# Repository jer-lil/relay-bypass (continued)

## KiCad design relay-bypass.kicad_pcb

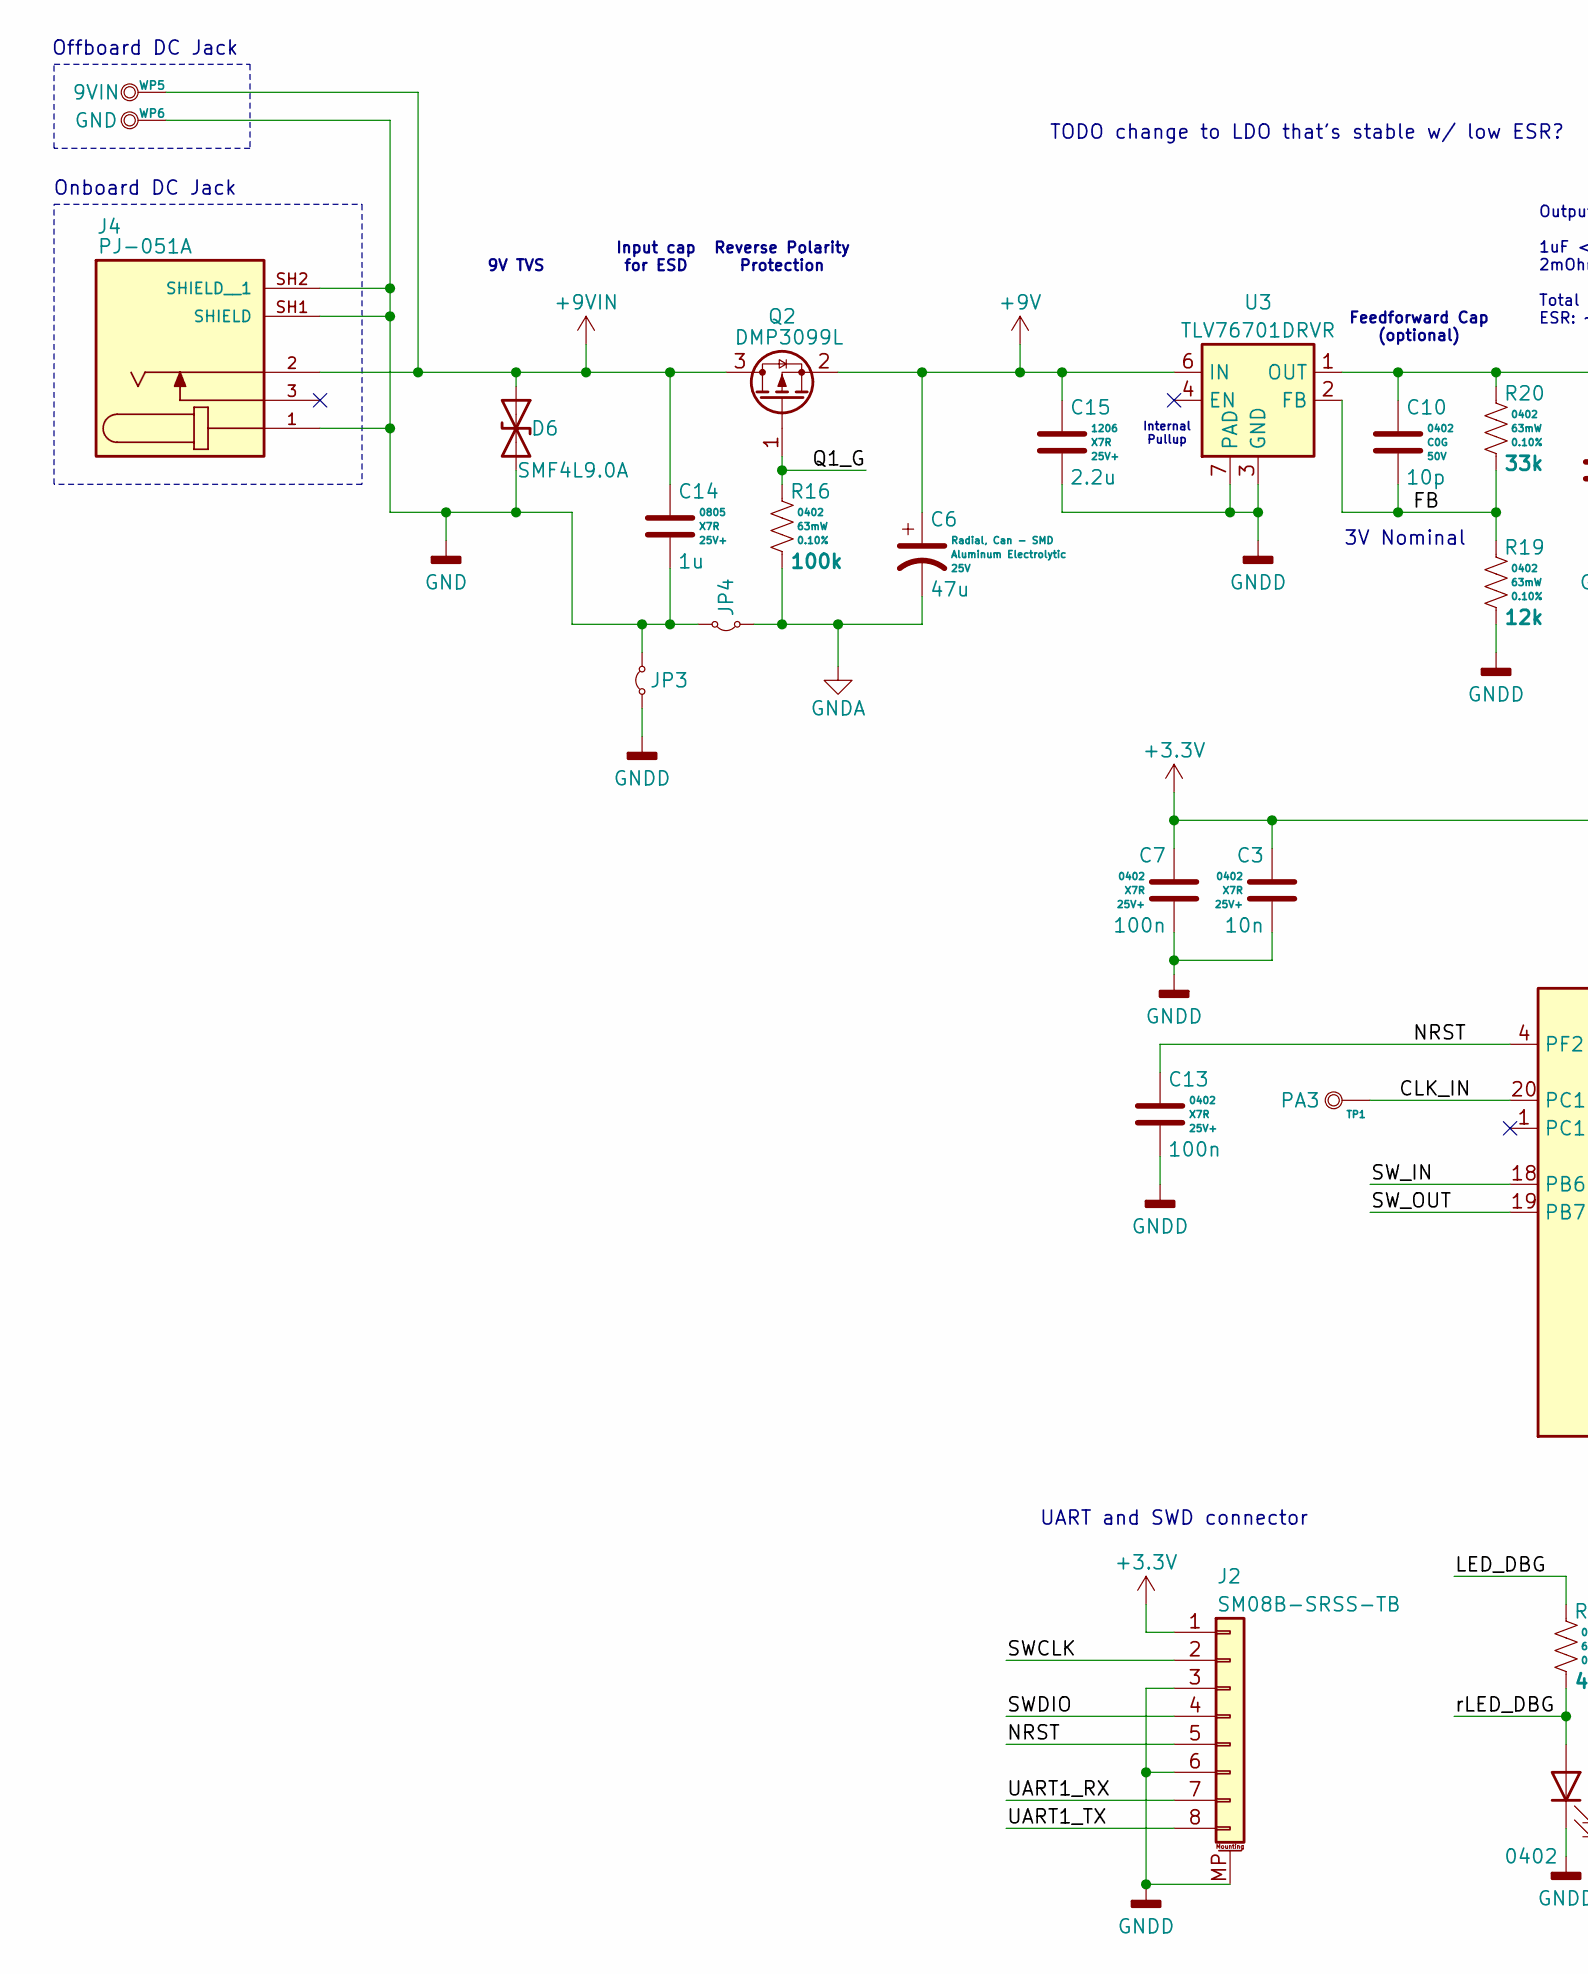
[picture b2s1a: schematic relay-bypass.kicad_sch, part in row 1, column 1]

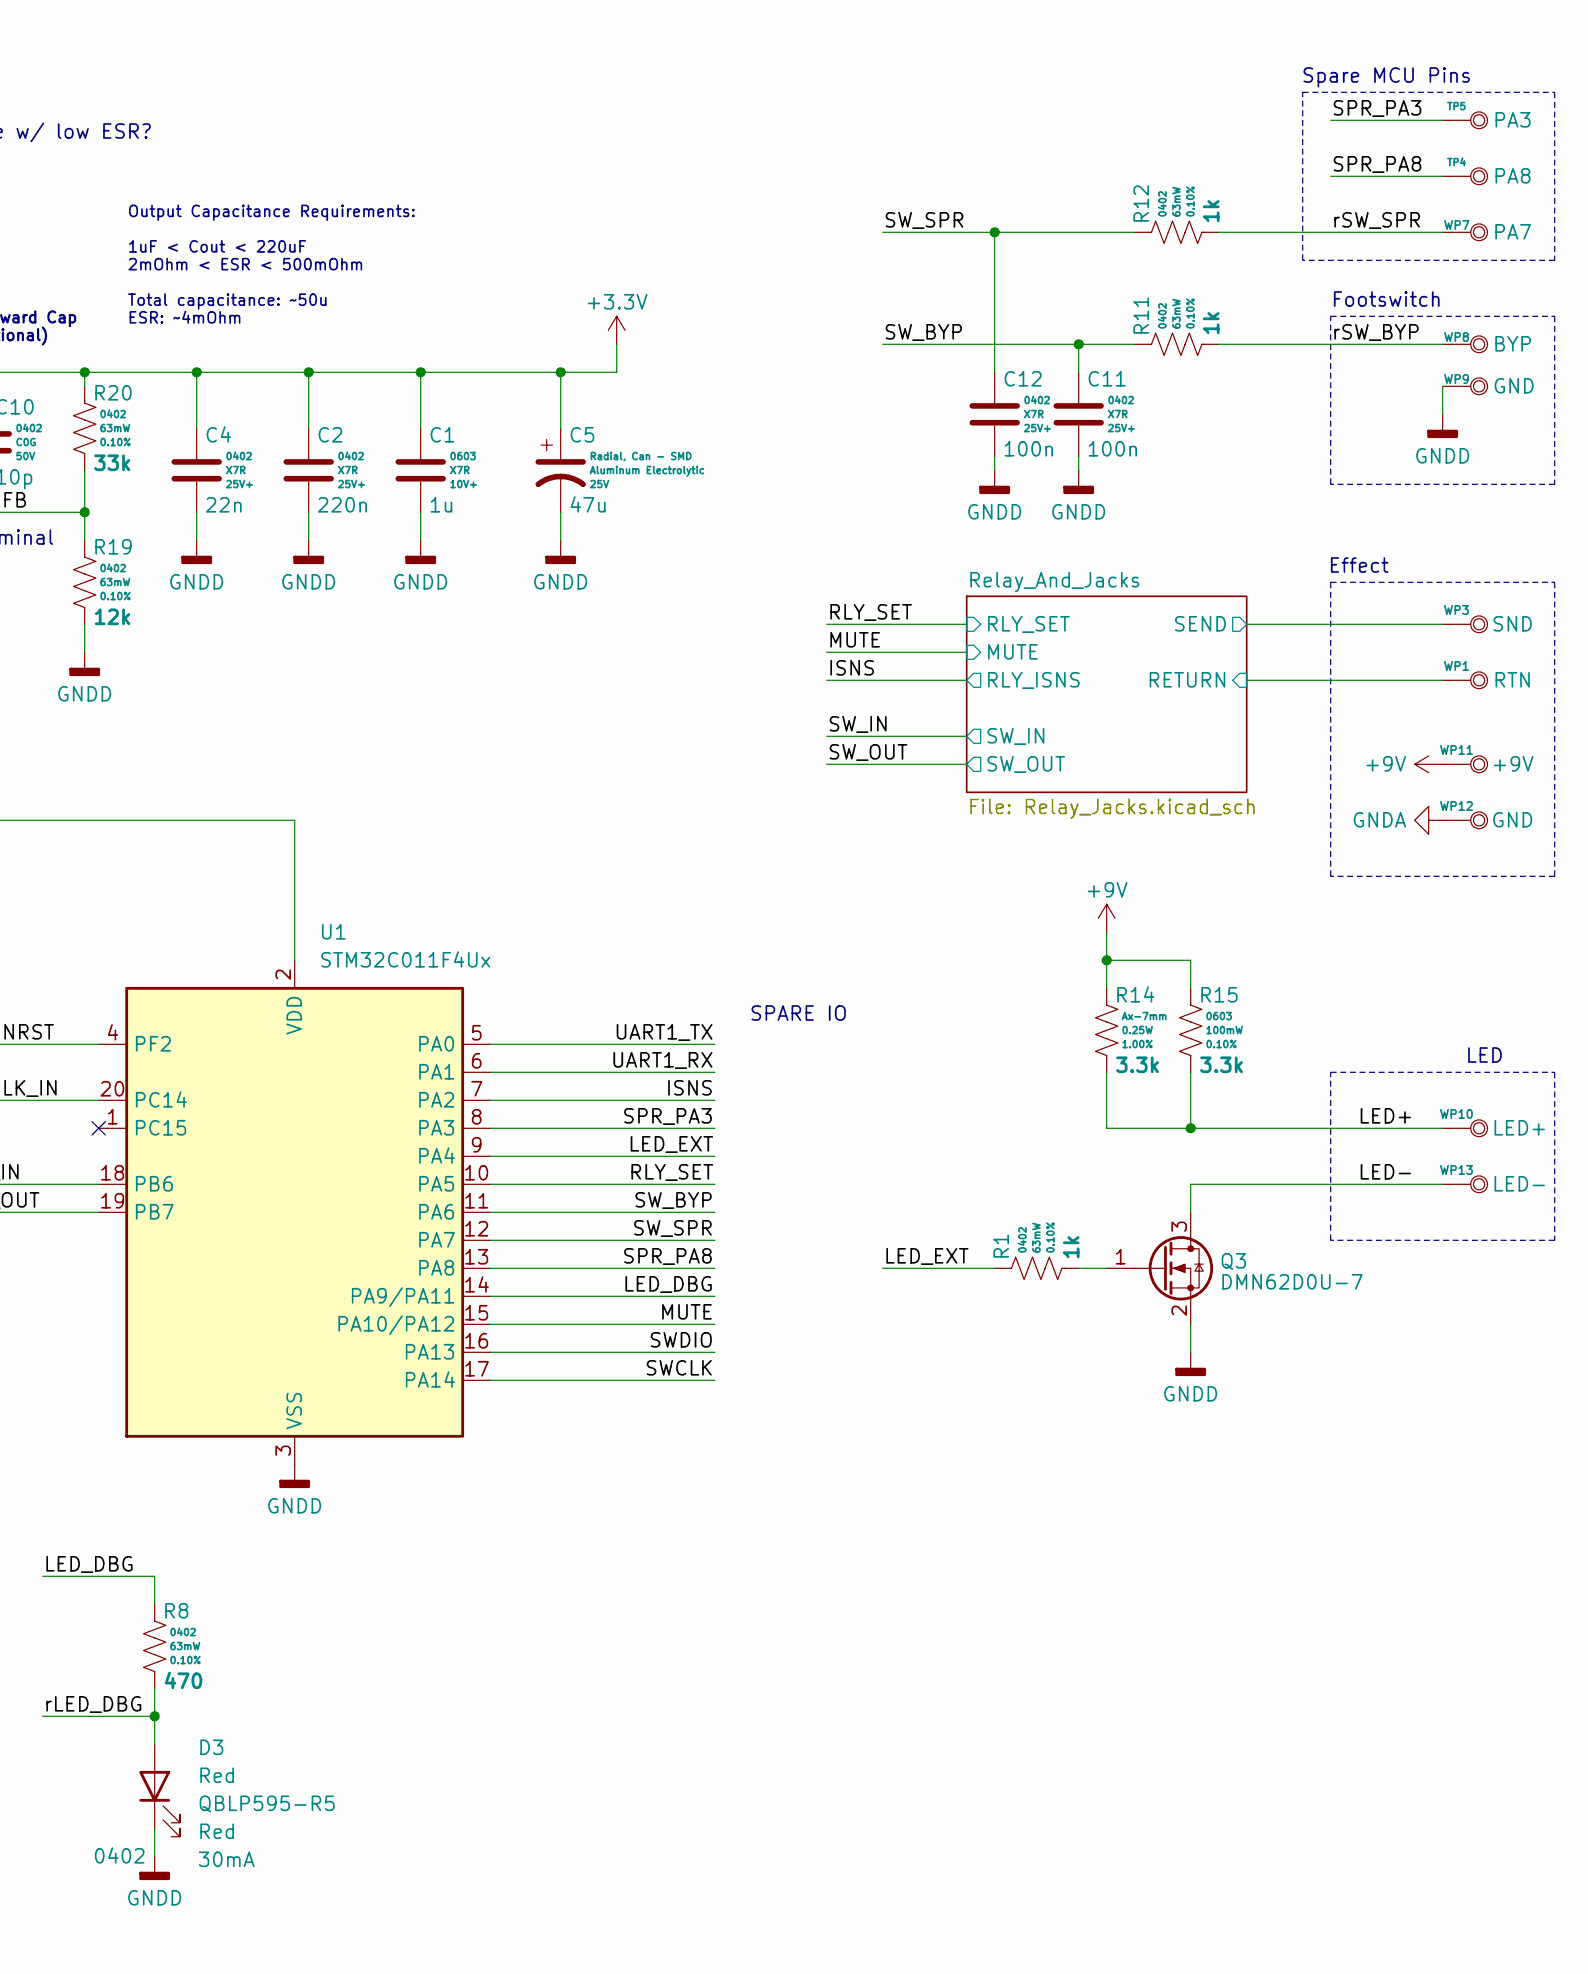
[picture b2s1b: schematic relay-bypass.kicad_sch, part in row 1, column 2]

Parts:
C1: 1u; C_0603_1608Metric; Voltage 10V+; Tolerance 10%; MPN C0603C105K8RACTU
C2: 220n; C_0402_1005Metric; Voltage 25V+; Tolerance 10%; MPN C0402C224K3RACTU
C3: 10n; C_0402_1005Metric; Voltage 25V+; Tolerance 10%; MPN C0402C103K3RACTU
C4: 22n; C_0402_1005Metric; Voltage 25V+; Tolerance 10%; MPN C0402C223K3RACTU
C5, C6: 47u; CP_Elec_6.3x5.8; Voltage 25V; Tolerance +/-20%; MPN EEE-FK1E470P
C7, C11, C12, C13: 100n; C_0402_1005Metric; Voltage 25V+; Tolerance 10%; MPN C0402C104K3RACTU
C10: 10p; C_0402_1005Metric; Voltage 50V; Tolerance +/-2%; MPN GRM1555C1H100GA01D
C14: 1u; C_0805_2012Metric; Voltage 25V+; Tolerance 10%; MPN C0805C105K3RACTU
C15: 2.2u; C_1206_3216Metric; Voltage 25V+; Tolerance 10%; MPN C1206C225K3RACTU
D3: Red; LED_0402_1005Metric; MPN QBLP595-R5
D6: SMF4L9.0A; D_SOD-123F; MPN SMF4L9.0A
J2: 8; JST_SH_BM08B-SRSS-TB_1x08-1MP_P1.00mm_Vertical; MPN SM08B-SRSS-TB
J4: 3; BarrelJack_CUI_PJ-051A; PARTREV 1.06
JP3, JP4: Jumper_2_Small_Bridged; SolderJumper-2_P1.3mm_Bridged2Bar_Pad1.0x1.5mm
Q2: DMP3099L; SOT-23; MPN DMP3099L
Q3: DMN62D0U-7; SOT-23; MPN DMN62D0U-7
R1, R11, R12: 1k; R_0402_1005Metric; Tolerance 0.10%; Voltage 50V; MPN RT0402BRD071KL
R8: 470; R_0402_1005Metric; Tolerance 0.10%; Voltage 50V; MPN RT0402BRD07470RL
R14: 3.3k; R_Axial_DIN0207_L6.3mm_D2.5mm_P7.5mm_Horizontal; Tolerance 1.00%; Voltage 250V; MPN MFR-25FBF52-3K3
R15: 3.3k; R_0603_1608Metric; Tolerance 0.10%; Voltage 75V; MPN RT0603BRD073K3L
R16: 100k; R_0402_1005Metric; Tolerance 0.10%; Voltage 50V; MPN RT0402BRD07100KL
R19: 12k; R_0402_1005Metric; Tolerance 0.10%; Voltage 50V; MPN RT0402BRD0712KL
R20: 33k; R_0402_1005Metric; Tolerance 0.10%; Voltage 50V; MPN RT0402BRD0733KL
TP1, TP5: PA3; TestPoint_PTH_H1.02mm_NoOutline
TP4: PA8; TestPoint_PTH_H1.02mm_NoOutline
U1: STM32C011F4Ux; ST_UFQFPN-20_3x3mm_P0.5mm
U3: TLV76701DRVR; WSON-6-1EP_2x2mm_P0.65mm_EP1x1.6mm; Voltage ADJ; MPN TLV76701DRVR
WP1: RTN; WirePad_H0.95mm_22-24AWG
WP3: SND; WirePad_H0.95mm_22-24AWG
WP5: 9VIN; WirePad_H0.95mm_22-24AWG
WP6, WP9, WP12: GND; WirePad_H0.95mm_22-24AWG
WP7: PA7; WirePad_H0.95mm_22-24AWG
WP8: BYP; WirePad_H0.95mm_22-24AWG
WP10: LED+; WirePad_H0.95mm_22-24AWG
WP11: +9V; WirePad_H0.95mm_22-24AWG
WP13: LED-; WirePad_H0.95mm_22-24AWG

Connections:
+3.3V: C1.1, C2.1, C3.1, C4.1, C5.1, C7.1, C10.1, J2.1, R20.1, U1.2 (VDD), U3.1 (OUT); also elsewhere on the board
+9V: C6.1, C15.1, Q2.2 (S), R14.1, R15.1, U3.6 (IN), WP11.1; also elsewhere on the board
+9VIN: C14.1, D6.1 (A1), J4.2, Q2.3 (D), WP5.1
/CLK_IN: TP1.1, U1.20 (PC14)
/FB: C10.2, R19.1, R20.2, U3.2 (FB)
/ISNS: U1.7 (PA2); also elsewhere on the board
/LED+: R14.2, R15.2, WP10.1
/LED-: Q3.3 (D), WP13.1
/LED_DBG: R8.1, U1.14 (PA9/PA11)
/LED_EXT: R1.1, U1.9 (PA4)
/MUTE: U1.15 (PA10/PA12); also elsewhere on the board
/NRST: C13.1, J2.5, U1.4 (PF2)
/Q1_G: Q2.1 (G), R16.1
/RLY_SET: U1.10 (PA5); also elsewhere on the board
/Relay_And_Jacks/RETURN: WP1.1; also elsewhere on the board
/Relay_And_Jacks/SEND: WP3.1; also elsewhere on the board
/SPR_PA3: TP5.1, U1.8 (PA3)
/SPR_PA8: TP4.1, U1.13 (PA8)
/SWCLK: J2.2, U1.17 (PA14)
/SWDIO: J2.4, U1.16 (PA13)
/SW_BYP: C11.1, R11.1, U1.11 (PA6)
/SW_IN: U1.18 (PB6); also elsewhere on the board
/SW_OUT: U1.19 (PB7); also elsewhere on the board
/SW_SPR: C12.1, R12.1, U1.12 (PA7)
/UART1_RX: J2.7, U1.6 (PA1)
/UART1_TX: J2.8, U1.5 (PA0)
/rLED_DBG: D3.2 (A), R8.2
/rSW_BYP: R11.2, WP8.1
/rSW_SPR: R12.2, WP7.1
GND: C14.2, D6.2 (A2), J4.1, J4.SH1 (SHIELD), J4.SH2 (SHIELD__1), JP3.2 (B), JP4.2 (B), WP6.1
GNDA: C6.2, JP4.1 (A), R16.2, WP12.1; also elsewhere on the board
GNDD: C1.2, C2.2, C3.2, C4.2, C5.2, C7.2, C11.2, C12.2, C13.2, C15.2, D3.1 (K), J2.3, J2.6, J2.MP (MountPin), JP3.1 (A), Q3.2 (S), R19.2, U1.3 (VSS), U3.3 (GND), U3.5 (GND), U3.7 (PAD), WP9.1; also elsewhere on the board
unnamed: Q3.1 (G), R1.2

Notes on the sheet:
Input cap for ESD
UART and SWD connector
Spare MCU Pins
Effect
9V TVS
TODO change to LDO that's stable w/ low ESR?
Reverse Polarity Protection
3V Nominal
Output Capacitance Requirements: 1uF < Cout < 220uF 2mOhm < ESR < 500mOhm Total capacitance: ~50u ESR: ~4mOhm
LED
Footswitch
Feedforward Cap (optional)
SPARE IO
Onboard DC Jack
Internal Pullup
Offboard DC Jack

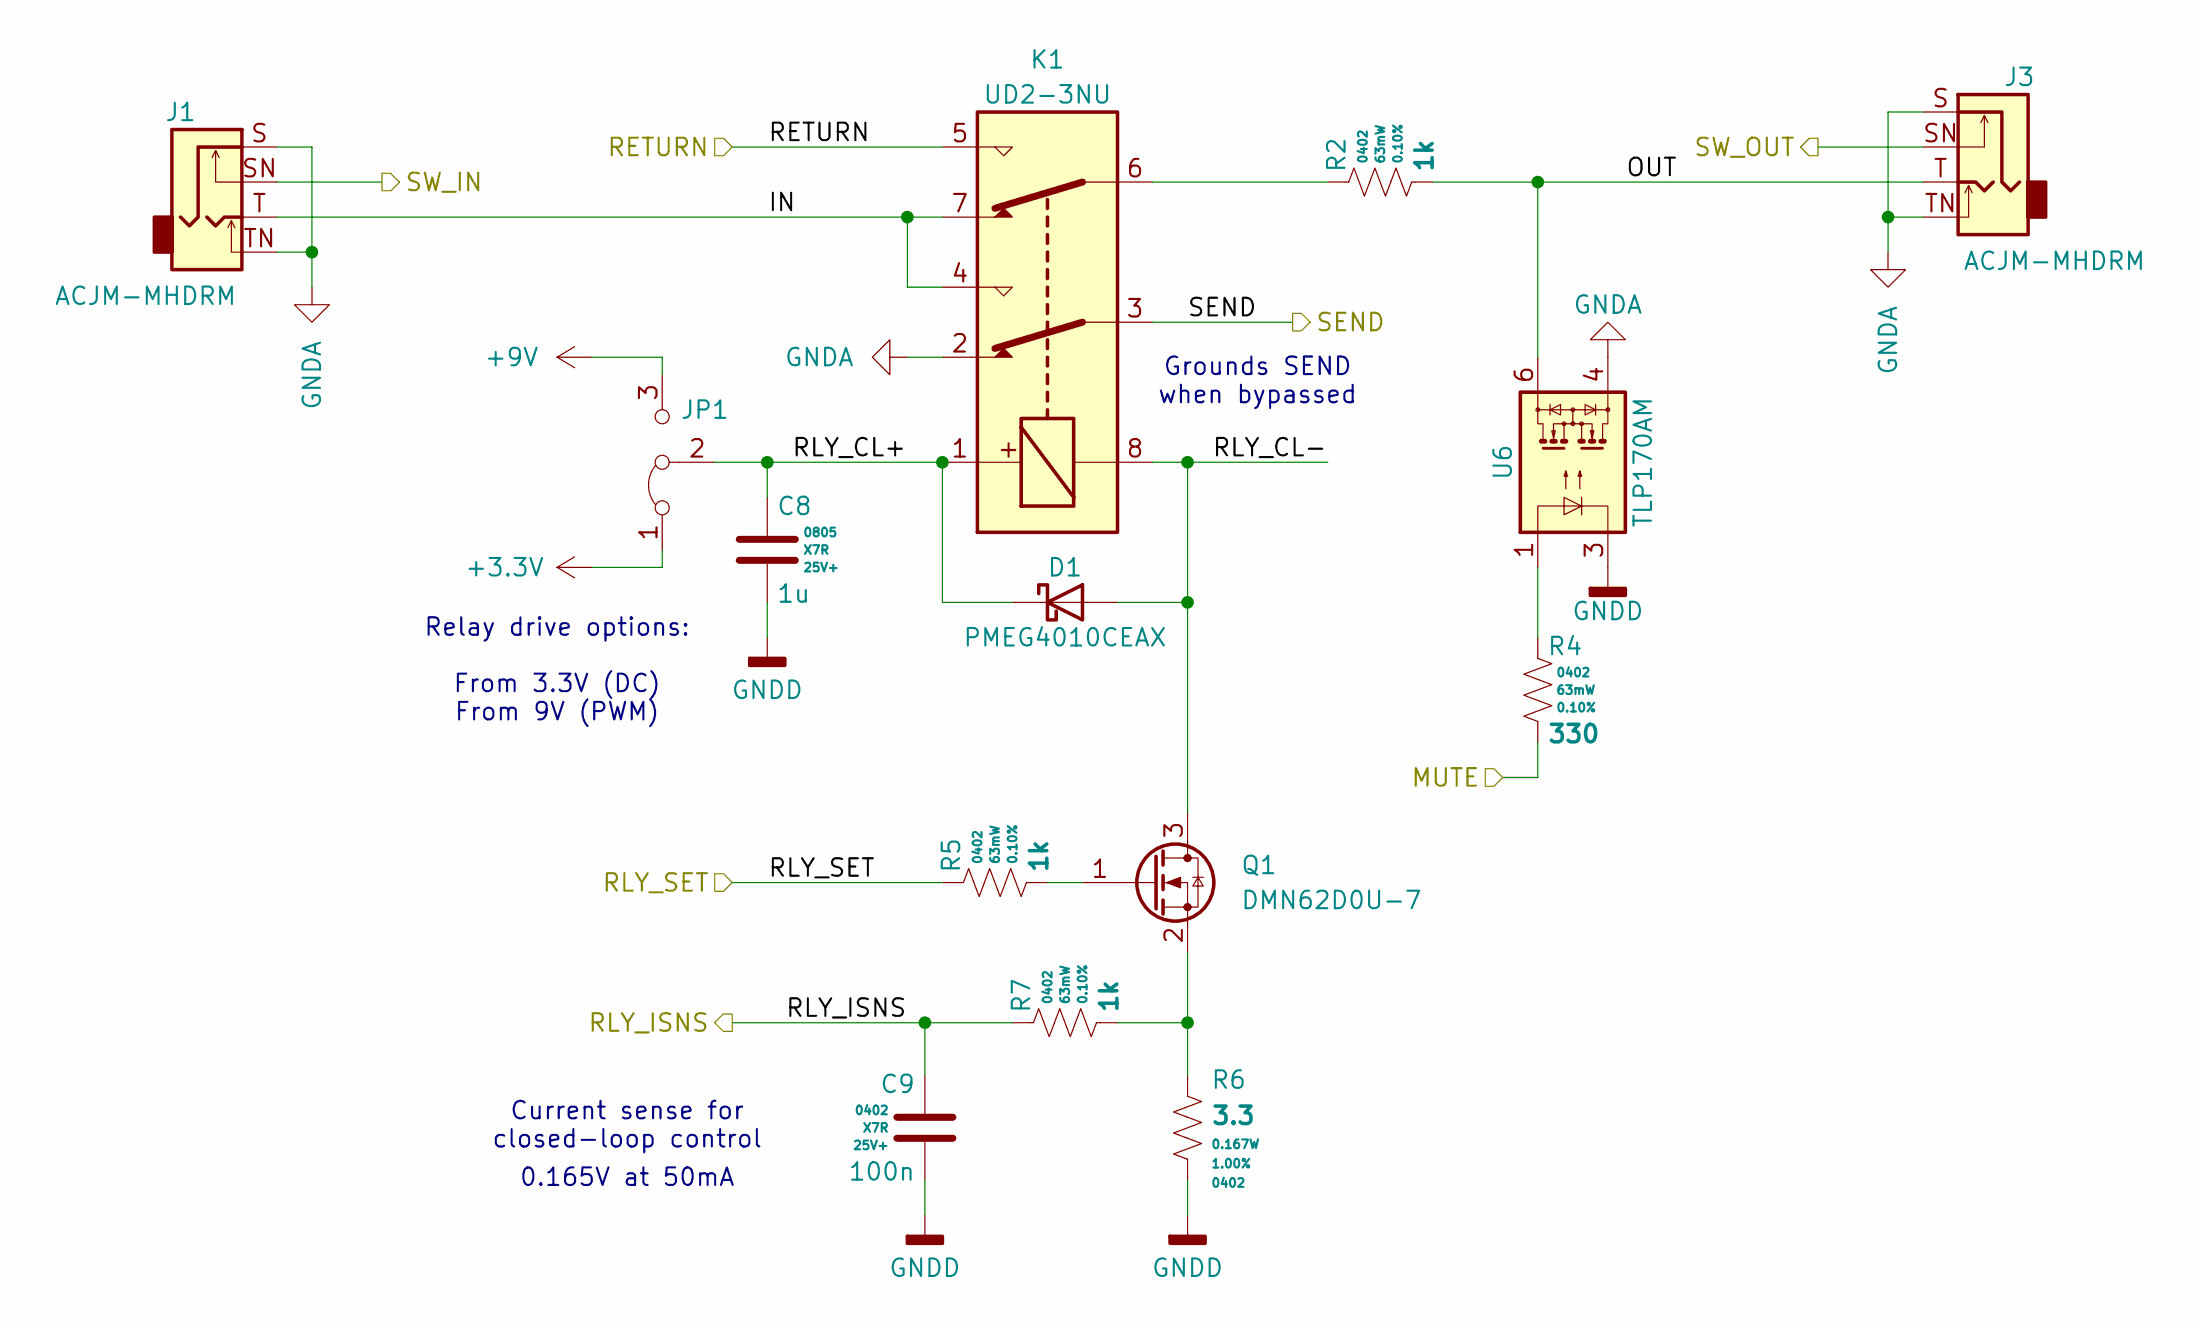
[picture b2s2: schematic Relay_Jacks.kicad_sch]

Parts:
C8: 1u; C_0805_2012Metric; Voltage 25V+; Tolerance 10%; MPN C0805C105K3RACTU
C9: 100n; C_0402_1005Metric; Voltage 25V+; Tolerance 10%; MPN C0402C104K3RACTU
D1: PMEG4010CEAX; D_SOD-323; Voltage 840 mV @ 1 A; MPN PMEG4010CEAX
J1, J3: 4; Amphenol_ACJM-MHDR(M); MPN ACJM-MHDRM
JP1: Jumper_3_Bridged12; SolderJumper-3_P1.3mm_Bridged12_Pad1.0x1.5mm
K1: IM05JR; UD23NU; MPN UD2-3NU
Q1: DMN62D0U-7; SOT-23; MPN DMN62D0U-7
R2, R5, R7: 1k; R_0402_1005Metric; Tolerance 0.10%; Voltage 50V; MPN RT0402BRD071KL
R4: 330; R_0402_1005Metric; Tolerance 0.10%; Voltage 50V; MPN RT0402BRD07330RL
R6: 3.3; R_0402_1005Metric; Tolerance 1.00%; Voltage 50V; MPN RL0510S-3R3-F
U6: TLP170AM; SO-4_4.4x3.9mm_P2.54mm; MPN TLP170AM

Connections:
+3.3V: JP1.1 (A); also elsewhere on the board
+9V: JP1.3 (B); also elsewhere on the board
/ISNS: C9.1, R7.1; also elsewhere on the board
/MUTE: R4.2; also elsewhere on the board
/RLY_SET: R5.1; also elsewhere on the board
/Relay_And_Jacks/IN: J1.T, K1.4, K1.7
/Relay_And_Jacks/OUT: J3.T, R2.2, U6.6
/Relay_And_Jacks/RETURN: K1.5; also elsewhere on the board
/Relay_And_Jacks/RLY_CL+: C8.1, D1.1 (K), JP1.2 (C), K1.1
/Relay_And_Jacks/RLY_CL-: D1.2 (A), K1.8, Q1.3 (D)
/Relay_And_Jacks/SEND: K1.3; also elsewhere on the board
/SW_IN: J1.SN; also elsewhere on the board
/SW_OUT: J3.SN; also elsewhere on the board
GNDA: J1.S, J1.TN, J3.S, J3.TN, K1.2, U6.4; also elsewhere on the board
GNDD: C8.2, C9.2, R6.2, U6.3; also elsewhere on the board
unnamed: K1.6, R2.1
unnamed: Q1.1 (G), R5.2
unnamed: Q1.2 (S), R6.1, R7.2
unnamed: R4.1, U6.1

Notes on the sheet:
Current sense for closed-loop control
Grounds SEND when bypassed
Relay drive options: From 3.3V (DC) From 9V (PWM)
0.165V at 50mA

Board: 2 copper layers, 60 parts (4 on the bottom side), 41 nets, no tracks yet.

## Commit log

2025-05-29 First commit, schematic ready for review + layout
2025-07-13 Added audio jacks based on recent decision
    Decided to make this a board that mounts to audio jacks on top face of a 125B enclosure. May also work for 1590B, TBD. Made most of the schematic changes.
2025-07-17 Schematic done?
2025-09-01 Committing uncommitted work, not sure what it was
2025-09-01 Added second project for exploring a single-jack side mounted version
2025-09-29 Pivoted to dual-jack version on opposing sides.
    125B only, using "innie" jacks. Solder-in-place.
2026-01-04 Scratchwork
